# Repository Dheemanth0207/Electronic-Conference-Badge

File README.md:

# Electronic Conference Badge

## Project Overview

This project investigates the design and development of a smart, energy-efficient electronic conference badge intended to replace traditional printed name tags used at events and meetings. The system is built around a compact microcontroller board, which controls a 3.52-inch e-paper display capable of showing attendee names, designations, or other event-specific content. Unlike conventional displays, e-paper offers excellent readability in various lighting conditions, including bright sunlight, while consuming very little power, making it ideal for multi-day usage on a single charge. 

The badge is designed to be interactive and easily programmable, featuring a set of physical buttons for input and wireless communication that allow it to connect with other badges or systems for capabilities such as contact exchange, activity tracking, or peer-to-peer messaging. A SD card reader also provides the flexibility to update the badge content without relying on an internet connection, making it useful in both connected and standalone scenarios

To reliably support all of these features, the hardware integrates a combination of power management circuits to ensure stable operation across different use cases. These include a voltage regulator and boost converter to provide the necessary voltages for the logic components and display. The board is powered by a 3.7V rechargeable battery and is charged or programmed via a USB Type-C connector. 

All design work, including schematic creation and PCB layout, was completed using the open-source KiCAD 9 design tool, ensuring that the board is optimized for surface-mount manufacturing. By combining low-power electronics, open-source design tools, and a thoughtful user interface, this badge system offers a modern, reusable, and sustainable alternative to traditional paper-based identification at events. 

## Hardware Preview

### Schematic

### PCB Layout

### 3D Render

## 🛠️ Requirements

To view, edit, or manufacture this project, the following software is required:

* **KiCad 9.0 or later**
* A computer running Windows, Linux, or macOS
* Optional: Gerber viewer for manufacturing file verification

## 📥 Installation

### 1. Install KiCad

Download and install the latest version of KiCad from the official website:

https://www.kicad.org/download/

Verify that KiCad is correctly installed by launching the application and opening the Project Manager.

### 2. Clone the Repository

```bash
git clone https://github.com/<your-username>/<repository-name>.git
cd <repository-name>
```

Alternatively, download the project as a ZIP file and extract it to your desired location.

### 3. Open the Project

1. Launch **KiCad 9**.
2. Select **File → Open Project**.
3. Navigate to the project directory.
4. Open the `.kicad_pro` file.

The project schematic, PCB layout, symbols, footprints, and manufacturing files will now be available through the KiCad Project Manager.

## 📂 Project Structure

```text
Project/
│
├── Hardware/
│   ├── Schematics/
│   ├── PCB/
│   ├── Libraries/
│   └── Manufacturing/
│
├── Documentation/
│   ├── Images/
│   └── Datasheets/
│
└── README.md
```

## 🔧 Editing the Design

### Schematic

1. Open the project in KiCad.
2. Click **Schematic Editor**.
3. Modify components, connections, or annotations as required.
4. Run **Electrical Rules Check (ERC)** before saving changes.

### PCB Layout

1. Open **PCB Editor**.
2. Update the PCB from the schematic if changes have been made.
3. Verify component placement and routing.
4. Run **Design Rules Check (DRC)** to identify any layout issues.

## 📤 Generating Manufacturing Files

To generate fabrication files:

1. Open the PCB Editor.
2. Select **File → Fabrication Outputs → Gerbers**.
3. Generate Gerber files for all required layers.
4. Generate drill files using **Generate Drill Files**.
5. Review the outputs using a Gerber viewer before sending them to a PCB manufacturer.

## 🔋 Hardware Features

* 3.52-inch E-Paper Display
* Low-power microcontroller platform
* Wireless communication capability
* Physical navigation buttons
* MicroSD card support
* USB Type-C charging and programming
* Rechargeable 3.7 V Li-ion battery support
* Integrated voltage regulation and boost conversion circuitry
* Surface-mount optimized PCB design

## 🤝 Contributing

Contributions, suggestions, and improvements are welcome. Please fork the repository, create a feature branch, and submit a pull request describing your changes.

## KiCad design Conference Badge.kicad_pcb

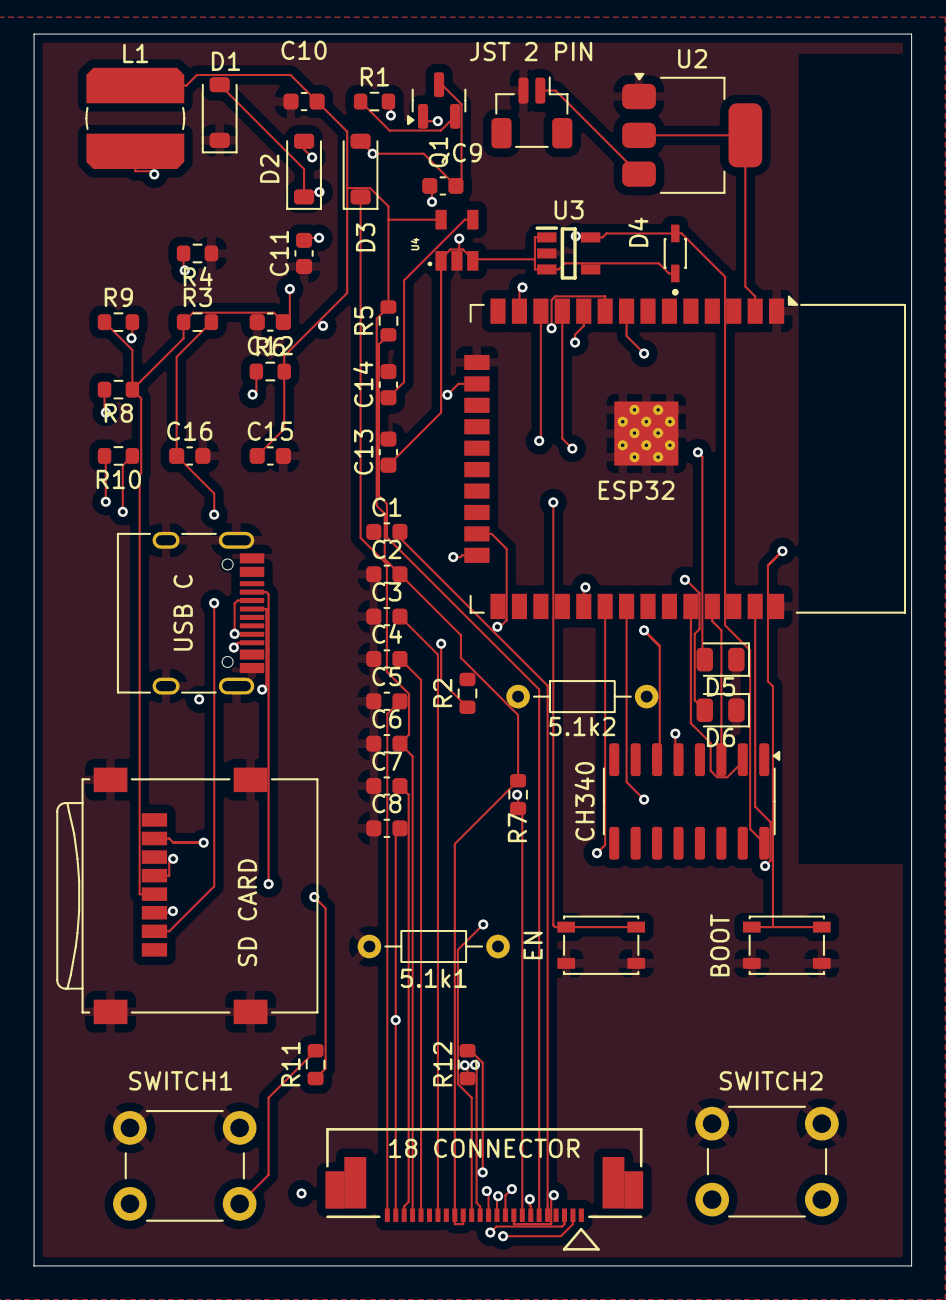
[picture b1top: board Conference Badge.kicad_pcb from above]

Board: 4 copper layers, 52.0 x 73.0 mm, 51 parts (0 on the bottom side), 47 nets.

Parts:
5.1k1, 5.1k2: R; R_Axial_DIN0204_L3.6mm_D1.6mm_P7.62mm_Horizontal
18 CONNECTOR : Conn_01x24; CON_524352471_MOL
BOOT: BOOT; SW_SPST_PTS810
C1, C2, C3, C4, C5, C6, C7, C8: 1uF/50V; C_0603_1608Metric
C9, C10: 4.7 uF; C_0603_1608Metric
C11, C12, C15: 10uF; C_0603_1608Metric
C13: 1uF; C_0603_1608Metric
C14: 22nF; C_0603_1608Metric
C16: 104; C_0603_1608Metric
CH340: CH340C; SOIC-16_3.9x9.9mm_P1.27mm
D1, D2, D3: MBR0530; D_SOD-123
D4: B5819WSHE3-TP; SOD2512X115N
D5, D6: LED; LED_0805_2012Metric
EN: EN; SW_SPST_PTS810
ESP32: ESP32-WROOM-32E; ESP32-WROOM-32D
JST 2 PIN: Battery_Cell; JST_SH_BM02B-SRSS-TB_1x02-1MP_P1.00mm_Vertical
L1: 10uH; L_Bourns_SDR0604
Q1: BSS138; SOT-23
R1: 0.47R; R_0603_1608Metric
R2, R3, R8, R11, R12: 10K; R_0603_1608Metric
R4: R; R_0603_1608Metric
R5: 10k/NC; R_0603_1608Metric
R6: 10K/NC; R_0603_1608Metric
R7: NC; R_0603_1608Metric
R9: 2.2K; R_0603_1608Metric
R10: 1K; R_0603_1608Metric
SD CARD: Micro_SD_Card; microSD_HC_Wuerth_693072010801
SWITCH1, SWITCH2: SW_Push; SW_PUSH_6mm
U2: AMS1117-3.3; SOT-223-3_TabPin2
U3: ME6217C33M5G; SOT23-5
U4: RT9193-33GB; SOT94P279X129-5N
USB C : USB_C_Receptacle_USB2.0; USB_C_Receptacle_HRO_TYPE-C-31-M-12

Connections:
+3V3: C12.1, CH340.16 (VCC), D4.A, R3.1, R8.1, R9.1, SD CARD.4 (VDD), U3.5 (OUT)
/SW1: EN.1, R8.2
/SW2: BOOT.1, C16.1, R3.2
BS: 18 CONNECTOR.8, R4.2, R7.1
EPD_3.3V: 18 CONNECTOR.15, 18 CONNECTOR.16, C2.2, C10.1, C15.1, L1.1, R5.2, R6.2, R7.2, U4.5 (VOUT)
GDR: 18 CONNECTOR.2, Q1.1 (G), R2.1
GND: 5.1k1.2, 5.1k2.2, 18 CONNECTOR.17, BOOT.2, C1.1, C2.1, C3.1, C4.1, C5.1, C6.1, C7.1, C8.1, C10.2, C11.1, C12.2, C13.2, C14.2, C15.2, C16.2, CH340.1 (GND), D1.1 (K), D5.1 (K), D6.1 (K), EN.2, ESP32.1 (GND), ESP32.15 (GND), ESP32.38 (GND), ESP32.39 (GND), JST 2 PIN.2 (-), R2.2, R4.1, SD CARD.6 (VSS), SD CARD.9 (SHIELD), SWITCH1.2, SWITCH2.2, U2.1 (GND), U3.2 (GND), U4.2 (GND), USB C.A1 (GND), USB C.A12 (GND), USB C.B1 (GND), USB C.B12 (GND), USB C.S1 (SHIELD)
IO2: ESP32.24 (IO2), R10.1
IO5: ESP32.29 (IO5), SD CARD.2 (DAT3/CD)
IO13: 18 CONNECTOR.13, ESP32.16 (IO13)
IO14: 18 CONNECTOR.14, ESP32.13 (IO14)
IO15: 18 CONNECTOR.12, ESP32.23 (IO15)
IO18: ESP32.30 (IO18), SD CARD.5 (CLK)
IO19: ESP32.31 (IO19), SD CARD.7 (DAT0)
IO23: ESP32.37 (IO23), SD CARD.3 (CMD)
IO25: 18 CONNECTOR.9, ESP32.10 (IO25)
IO26: 18 CONNECTOR.10, ESP32.11 (IO26)
IO27: 18 CONNECTOR.11, ESP32.12 (IO27)
IO32: ESP32.8 (IO32), R11.1
IO33: ESP32.9 (IO33), R12.1
unnamed: JST 2 PIN.1 (+), U2.3 (VI)
unnamed: C9.1, D1.2 (A), D2.1 (K)
unnamed: C9.2, D3.2 (A), L1.2, Q1.3 (D)
unnamed: D5.2 (A), R9.2
unnamed: D6.2 (A), R10.2
unnamed: 5.1k1.1, USB C.A5 (CC1)
unnamed: 5.1k2.1, USB C.B5 (CC2)
unnamed: 18 CONNECTOR.5, C1.2
unnamed: 18 CONNECTOR.18, C3.2
unnamed: 18 CONNECTOR.20, C4.2
unnamed: 18 CONNECTOR.22, C7.2
unnamed: 18 CONNECTOR.24, C5.2
unnamed: Q1.2 (S), R1.1
unnamed: R11.2, SWITCH1.1
unnamed: R12.2, SWITCH2.1
unnamed: ESP32.2 (VDD), U2.2 (VO)
unnamed: C14.1, U4.4 (BP)
unnamed: CH340.5 (UD+), USB C.A6 (D+)
unnamed: CH340.6 (UD-), USB C.B7 (D-)
PREVGH: 18 CONNECTOR.21, C6.2, D3.1 (K)
PREVGL: 18 CONNECTOR.23, C8.2, D2.2 (A)
RESE: 18 CONNECTOR.3, R1.2
RXD ESP32: CH340.3 (RXD), ESP32.35 (TXD0/IO1)
TSCL: 18 CONNECTOR.6, R5.1
TSDA: 18 CONNECTOR.7, R6.1
TXD ESP32: CH340.2 (TXD), ESP32.34 (RXD0/IO3)
VDD5V: C11.2, C13.1, D4.C, U3.1 (IN), U3.3 (CE), U4.1 (VIN), U4.3 (EN)

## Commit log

2026-06-05 Enhance README with detailed project description
    Expanded project description to include details about the microcontroller, e-paper display, interactivity, and power management features.
2026-06-05 Refine README for clarity and conciseness
2026-06-05 Uploaded files
2026-06-05 Update README for project overview and details
    Reformatted README to improve structure and clarity.
2026-06-05 Add ConferenceBadge.kicad_sym file
2026-06-05 Rename MSc_Project.bak to ConferenceBadge.bak
2026-06-05 Rename Msc Project.bak to Conference Badge.bak
2026-06-05 Rename Msc Project.csv to Conference Badge.csv
2026-06-05 Rename Msc Project.kicad_dru to Conference Badge.kicad_dru
2026-06-05 Add Conference Badge PCB file
2026-06-05 Rename Msc Project.kicad_sch-bak to Conference Badge.kicad_sch-bak
2026-06-05 Rename Msc Project.kicad_prl to Conference Badge.kicad_prl
2026-06-05 Rename Msc Project.kicad_pro to Conference Badge.kicad_pro
2026-06-05 Rename Msc Project.kicad_sch to Conference Badge.kicad_sch
2026-06-05 Rename Msc Project.kicad_sym to Conference Badge.kicad_sym
2026-06-05 Add requirements and installation instructions to README
